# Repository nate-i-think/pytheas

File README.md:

# about pytheas
Pytheas is a custom ATSAMD21G18A-based (Cortex-M0+, arduino-compatible) flight controller which I have designed for a self-landing, thrust vectoring rocket which is being built by [Princeton Rocketry](https://www.princetonrocketry.com/) at Princeton University. Anyone is welcome to integrate it into their projects as long as they provide appropriate credit. However, no technical support is provided.

# features
 - ATSAMD21G18A microprocessor
   - Programmable via SWD (TagConnect, half-pitch DuPont) and USB
   - 10 exposed GPIO (plus 5 more extras in half-pitch)
   - Exposed I2C (recomended to connect GPS)
   - Everything else you'd expect
 - BMP390 Pressure Sensor
 - LSM6DSOXTR 6-Axis IMU
 - Power Regulation:
   - 5V @ 9A out (buck) with lots of capacitence  
   - 3v3 @ 1A out (LDO)
   - ~6–12V in

# renderings

# layers

# schematic

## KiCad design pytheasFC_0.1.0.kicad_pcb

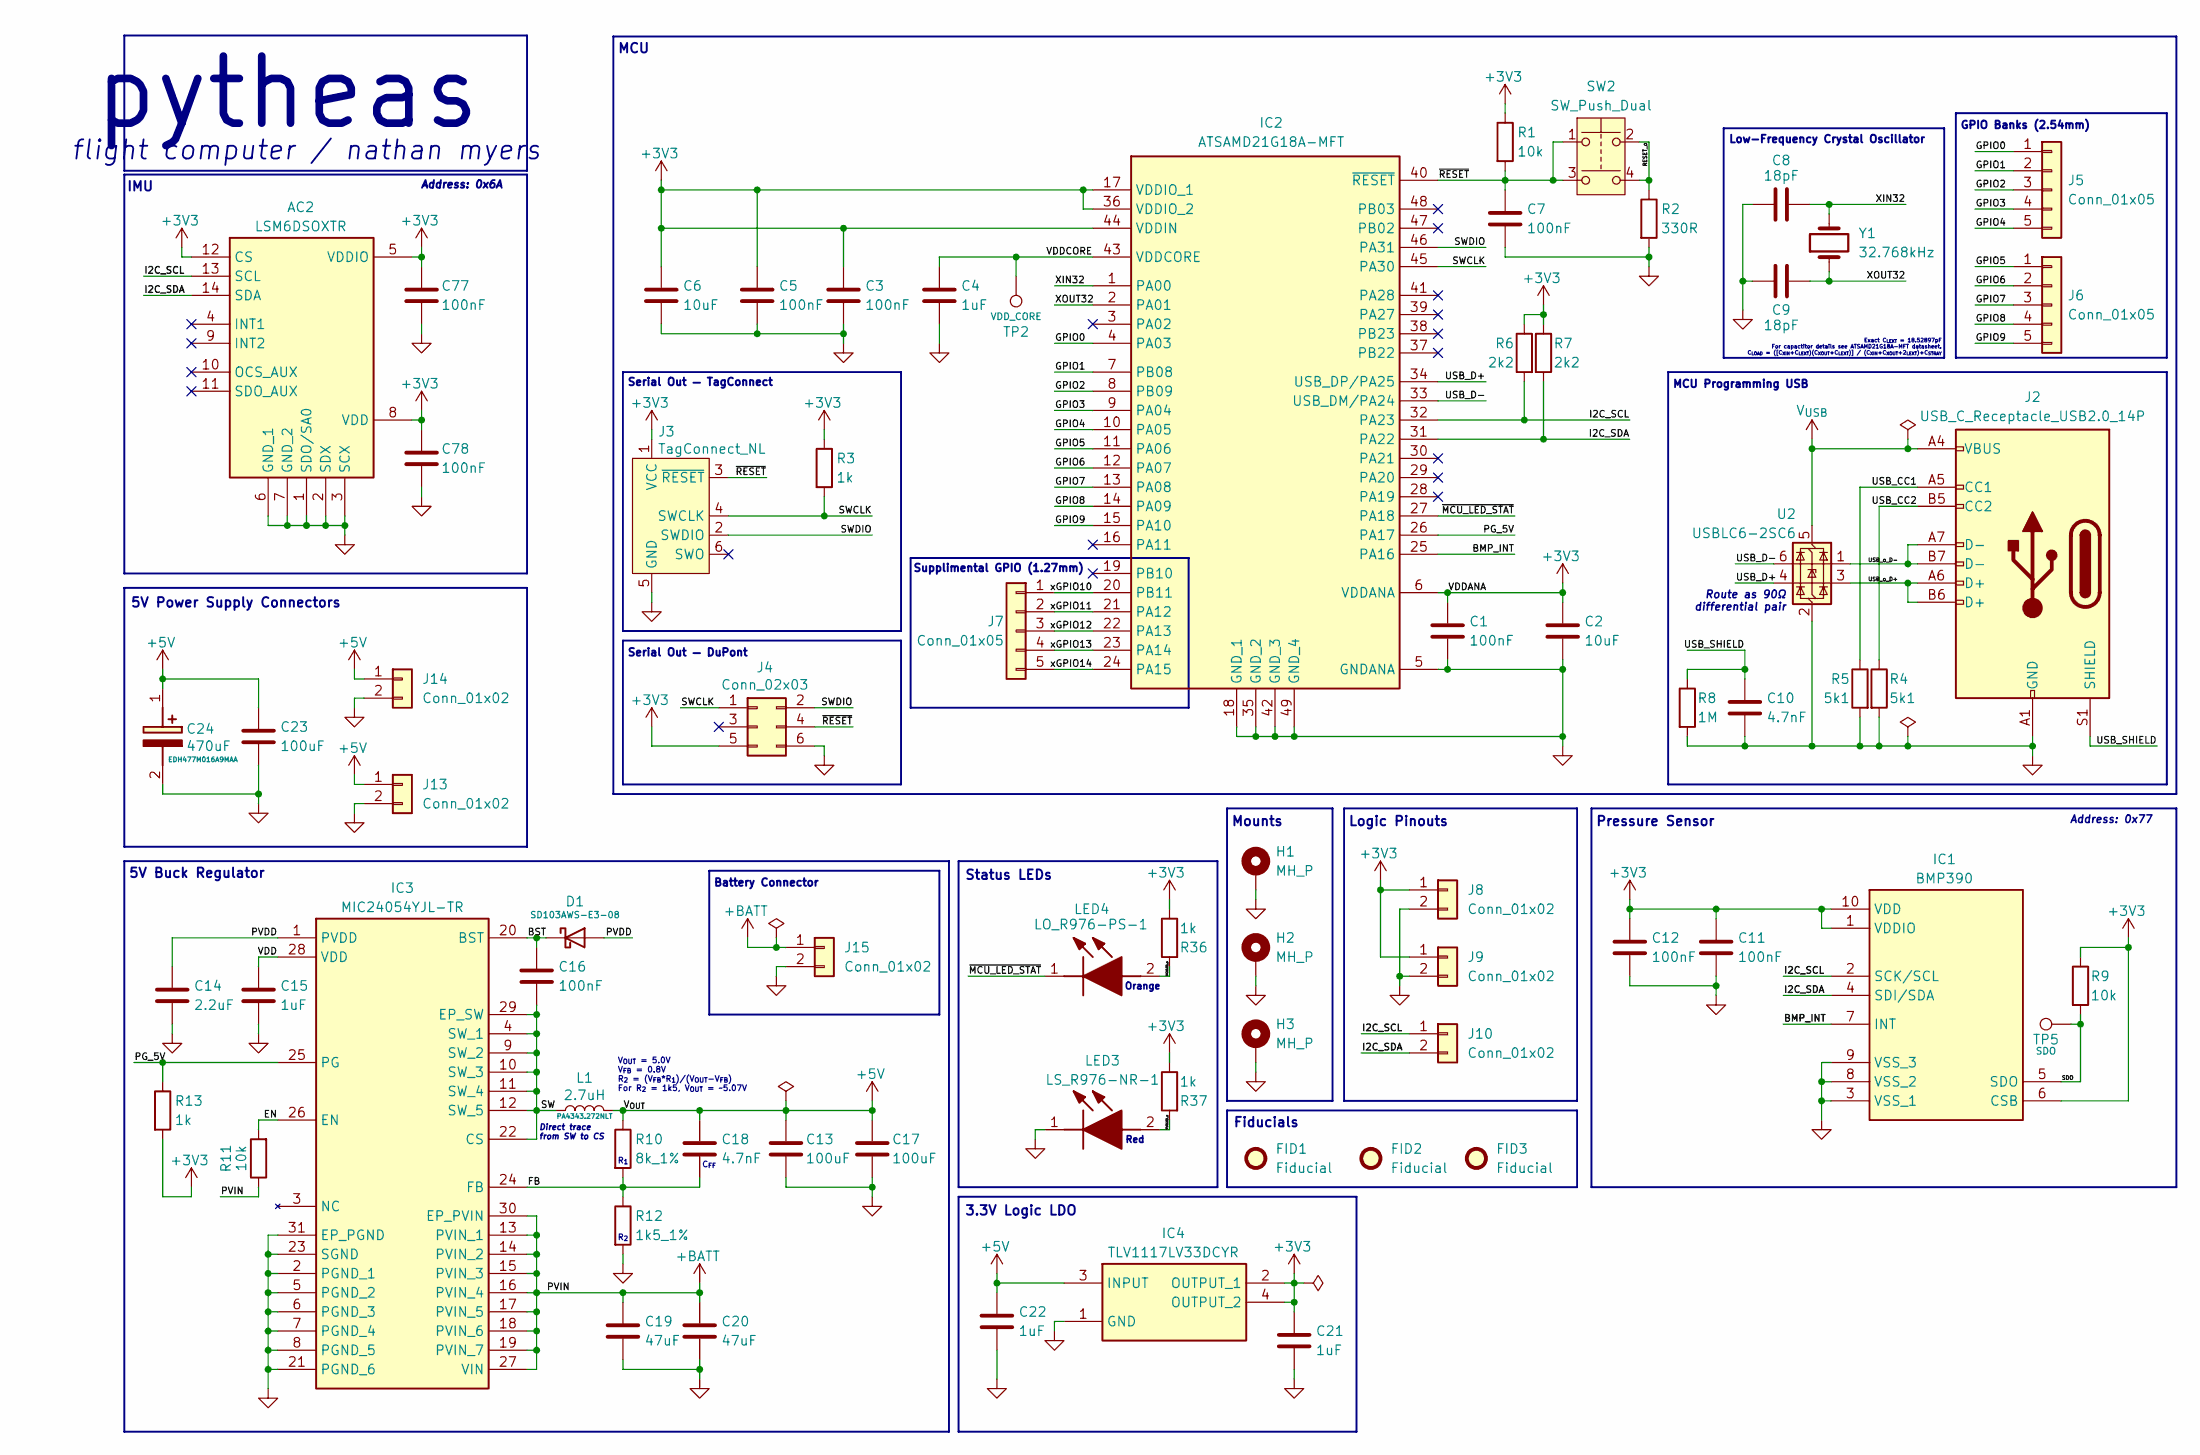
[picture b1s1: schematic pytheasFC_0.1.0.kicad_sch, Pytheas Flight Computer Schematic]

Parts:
AC2: LSM6DSOXTR; LGA-14_1; Mouser Part Number 511-LSM6DSOXTR
C1, C3, C5, C7, C11, C12, C16, C77, C78: 100nF; C_0402_1005Metric
C2, C6: 10uF; C_0805_2012Metric
C4, C15, C21, C22: 1uF; C_0805_2012Metric
C8, C9: 18pF; C_0402_1005Metric
C10, C18: 4.7nF; C_0402_1005Metric
C13, C17, C23: 100uF; C_1206_3216Metric
C14: 2.2uF; C_0805_2012Metric
C19, C20: 47uF; C_1206_3216Metric
C24: 470uF; CAPAE830X1050N; Mouser Part Number 80-EDH477M016A9MAA
D1: SD103AWS-E3-08; SOD2713X115N; Part Number SD103AWS-E3-08
FID1, FID2, FID3: Fiducial; Fiducial_1mm_Mask2mm
H1, H2, H3: MH_P; MountingHole_2.2mm_M2_Pad_Via
IC1: BMP390; Mouser Part Number 262-BMP390
IC2: ATSAMD21G18A-MFT; QFN50P700X700X90-49N-D; Mouser Part Number 556-ATSAMD21G18A-MFT
IC3: MIC24054YJL-TR; MIC24054YJLTR; Mouser Part Number 998-MIC24054YJLTR
IC4: TLV1117LV33DCYR; SOT230P700X180-4N; Mouser Part Number 595-TLV1117LV33DCYR
J2: USB_C_Receptacle_USB2.0_14P; USB_C_Receptacle_GCT_USB4105-xx-A_16P_TopMnt_Horizontal
J3: TagConnect_NL; Tag-Connect_TC2030-IDC-NL_2x03_P1.27mm_Vertical
J4: Conn_02x03; PinHeader_2x03_P1.27mm_Vertical
J5, J6: Conn_01x05; PinHeader_1x05_P2.54mm_Horizontal
J7: Conn_01x05; PinHeader_1x05_P1.27mm_Vertical
J8, J9, J10, J13, J14, J15: Conn_01x02; PinHeader_1x02_P2.54mm_Horizontal
L1: 2.7uH; INDPM140128X650N; Part Number PA4343.272NLT
LED3: LS_R976-NR-1; LEDC2012X40N; Mouser Part Number 720-LSR976-NR-1
LED4: LO_R976-PS-1; LEDC2012X90N; Mouser Part Number 720-LOR976-PS-1
R1, R9, R11: 10k; R_0402_1005Metric
R2: 330R; R_0402_1005Metric
R3, R13, R36, R37: 1k; R_0402_1005Metric
R4, R5: 5k1; R_0402_1005Metric
R6, R7: 2k2; R_0402_1005Metric
R8: 1M; R_0402_1005Metric
R10: 8k_1%; R_0402_1005Metric
R12: 1k5_1%; R_0402_1005Metric
SW2: SW_Push_Dual; FSM2J_1; Part Number 2-1437565-8
TP2: VDD_CORE; TestPoint_Pad_D2.0mm
TP5: SDO; TestPoint_Pad_D2.0mm
U2: USBLC6-2SC6; SOT-23-6
Y1: 32.768kHz; ECX-31B; Part Number ECS-.327-12.5-34B-TR

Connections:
+3V3: AC2.5 (VDDIO), AC2.8 (VDD), AC2.12 (CS), C1.1, C2.1, C3.1, C5.1, C6.1, C11.1, C12.1, C21.1, C77.1, C78.1, IC1.1 (VDDIO), IC1.6 (CSB), IC1.10 (VDD), IC2.6 (VDDANA), IC2.17 (VDDIO_1), IC2.36 (VDDIO_2), IC2.44 (VDDIN), IC4.2 (OUTPUT_1), IC4.4 (OUTPUT_2), J3.1 (VCC), J4.5, J8.1, J9.1, R1.1, R3.1, R6.1, R7.1, R9.1, R13.2, R36.1, R37.1
+5V: C13.1, C17.1, C18.1, C22.1, C23.1, C24.1 (+), IC4.3 (INPUT), J13.1, J14.1, L1.2, R10.1
+BATT: C19.1, C20.1, IC3.13 (PVIN_1), IC3.14 (PVIN_2), IC3.15 (PVIN_3), IC3.16 (PVIN_4), IC3.17 (PVIN_5), IC3.18 (PVIN_6), IC3.19 (PVIN_7), IC3.27 (VIN), IC3.30 (EP_PVIN), J15.1, R11.1
/BMP_INT: IC1.7 (INT), IC2.25 (PA16)
/BST: C16.1, D1.1 (K), IC3.20 (BST)
/EN: IC3.26 (EN), R11.2
/FB: C18.2, IC3.24 (FB), R10.2, R12.1
/GPIO0: IC2.4 (PA03), J5.1
/GPIO1: IC2.7 (PB08), J5.2
/GPIO2: IC2.8 (PB09), J5.3
/GPIO3: IC2.9 (PA04), J5.4
/GPIO4: IC2.10 (PA05), J5.5
/GPIO5: IC2.11 (PA06), J6.1
/GPIO6: IC2.12 (PA07), J6.2
/GPIO7: IC2.13 (PA08), J6.3
/GPIO8: IC2.14 (PA09), J6.4
/GPIO9: IC2.15 (PA10), J6.5
/I2C_SCL: AC2.13 (SCL), IC1.2 (SCK/SCL), IC2.32 (PA23), J10.1, R6.2
/I2C_SDA: AC2.14 (SDA), IC1.4 (SDI/SDA), IC2.31 (PA22), J10.2, R7.2
/MCULED_o: LED4.2 (A), R36.2
/PG_5V: IC2.26 (PA17), IC3.25 (PG), R13.1
/PVDD: C14.1, D1.2 (A), IC3.1 (PVDD)
/PWRLED_o: LED3.2 (A), R37.2
/RESET_o: R2.1, SW2.2, SW2.4
/SDO: IC1.5 (SDO), R9.2, TP5.1
/SW: C16.2, IC3.4 (SW_1), IC3.9 (SW_2), IC3.10 (SW_3), IC3.11 (SW_4), IC3.12 (SW_5), IC3.22 (CS), IC3.29 (EP_SW), L1.1
/SWCLK: IC2.45 (PA30), J3.4 (SWCLK), J4.1, R3.2
/SWDIO: IC2.46 (PA31), J3.2 (SWDIO), J4.2
/USB_CC1: J2.A5 (CC1), R5.1
/USB_CC2: J2.B5 (CC2), R4.1
/USB_D+: IC2.34 (USB_DP/PA25), U2.4 (I/O2)
/USB_D-: IC2.33 (USB_DM/PA24), U2.6 (I/O1)
/USB_SHIELD: C10.1, J2.S1 (SHIELD), R8.1
/USB_o_D+: J2.A6 (D+), J2.B6 (D+), U2.3 (I/O2)
/USB_o_D-: J2.A7 (D-), J2.B7 (D-), U2.1 (I/O1)
/VDD: C15.1, IC3.28 (VDD)
/VDDCORE: C4.1, IC2.43 (VDDCORE), TP2.1
/XIN32: C8.2, IC2.1 (PA00), Y1.2
/XOUT32: C9.1, IC2.2 (PA01), Y1.1
/xGPIO10: IC2.20 (PB11), J7.1
/xGPIO11: IC2.21 (PA12), J7.2
/xGPIO12: IC2.22 (PA13), J7.3
/xGPIO13: IC2.23 (PA14), J7.4
/xGPIO14: IC2.24 (PA15), J7.5
/~MCU_LED_STAT: IC2.27 (PA18), LED4.1 (K)
/~RESET: C7.1, IC2.40 (~RESET), J3.3 (~RESET), J4.4, R1.2, SW2.1, SW2.3
GND: AC2.1 (SDO/SA0), AC2.2 (SDX), AC2.3 (SCX), AC2.6 (GND_1), AC2.7 (GND_2), C1.2, C2.2, C3.2, C4.2, C5.2, C6.2, C7.2, C8.1, C9.2, C10.2, C11.2, C12.2, C13.2, C14.2, C15.2, C17.2, C19.2, C20.2, C21.2, C22.2, C23.2, C24.2 (-), C77.2, C78.2, H1.1, H2.1, H3.1, IC1.3 (VSS_1), IC1.8 (VSS_2), IC1.9 (VSS_3), IC2.5 (GNDANA), IC2.18 (GND_1), IC2.35 (GND_2), IC2.42 (GND_3), IC2.49 (GND_4), IC3.2 (PGND_1), IC3.5 (PGND_2), IC3.6 (PGND_3), IC3.7 (PGND_4), IC3.8 (PGND_5), IC3.21 (PGND_6), IC3.23 (SGND), IC3.31 (EP_PGND), IC4.1 (GND), J2.A1 (GND), J2.A12 (GND), J2.B1 (GND), J2.B12 (GND), J3.5 (GND), J4.6, J8.2, J9.2, J13.2, J14.2, J15.2, LED3.1 (K), R2.2, R4.2, R5.2, R8.2, R12.2, U2.2 (GND)
V_{USB}: J2.A4 (VBUS), J2.A9 (VBUS), J2.B4 (VBUS), J2.B9 (VBUS), U2.5 (VBUS)

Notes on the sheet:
Address: 0x6A
Pressure Sensor
Low-Frequency Crystal Oscillator
5V Buck Regulator
5V Power Supply Connectors
Serial Out — TagConnect
Logic Pinouts
Route as 90Ω differential pair
Fiducials
Address: 0x77
R_{1}
IMU
MCU
Orange
Direct trace from SW to CS
Mounts
Serial Out — DuPont
R_{2}
Battery Connector
C_{FF}
V_{OUT} = 5.0V V_{FB} = 0.8V R_{2} = (V_{FB}*R_{1})/(V_{OUT}-V_{FB}) For R_{2} = 1k5, V_{OUT} = ~5.07V
flight computer / nathan myers
GPIO Banks (2.54mm)
Exact C_{LEXT} = 18.52897pF For capactitor details see ATSAMD21G18A-MFT datasheet. C_{LOAD} = ([C_{XIN}+C_{LEXT})(C_{XOUT}+C_{LEXT})] / (C_{XIN}+C_{XOUT}+2_{LEXT})+C_{STRAY}
Status LEDs
Supplimental GPIO (1.27mm)
MCU Programming USB
3.3V Logic LDO
Red
pytheas

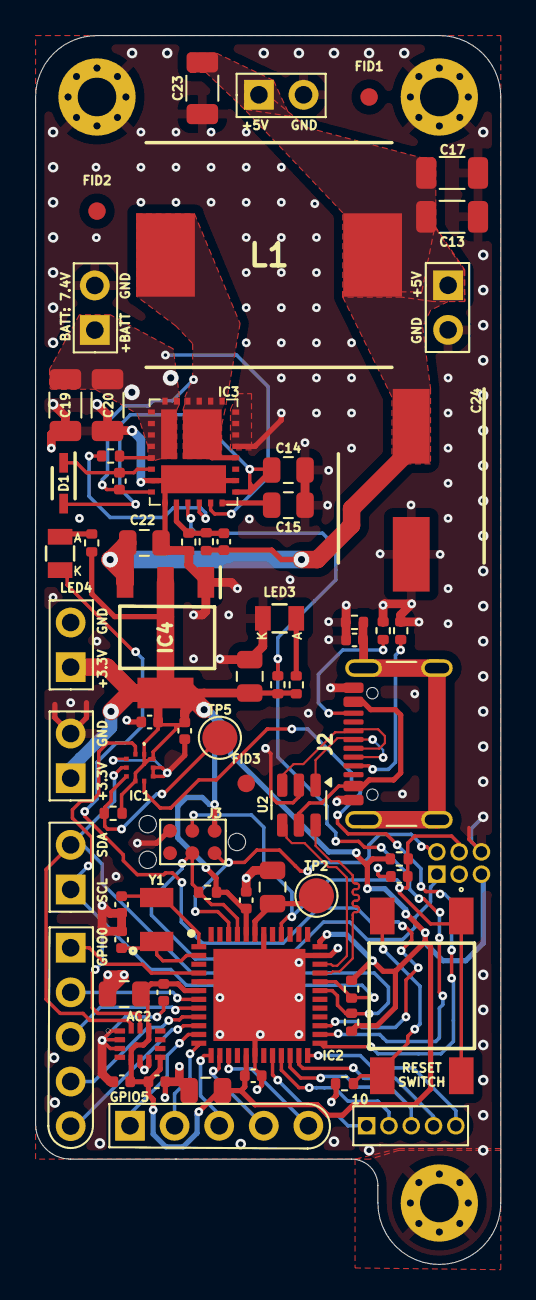
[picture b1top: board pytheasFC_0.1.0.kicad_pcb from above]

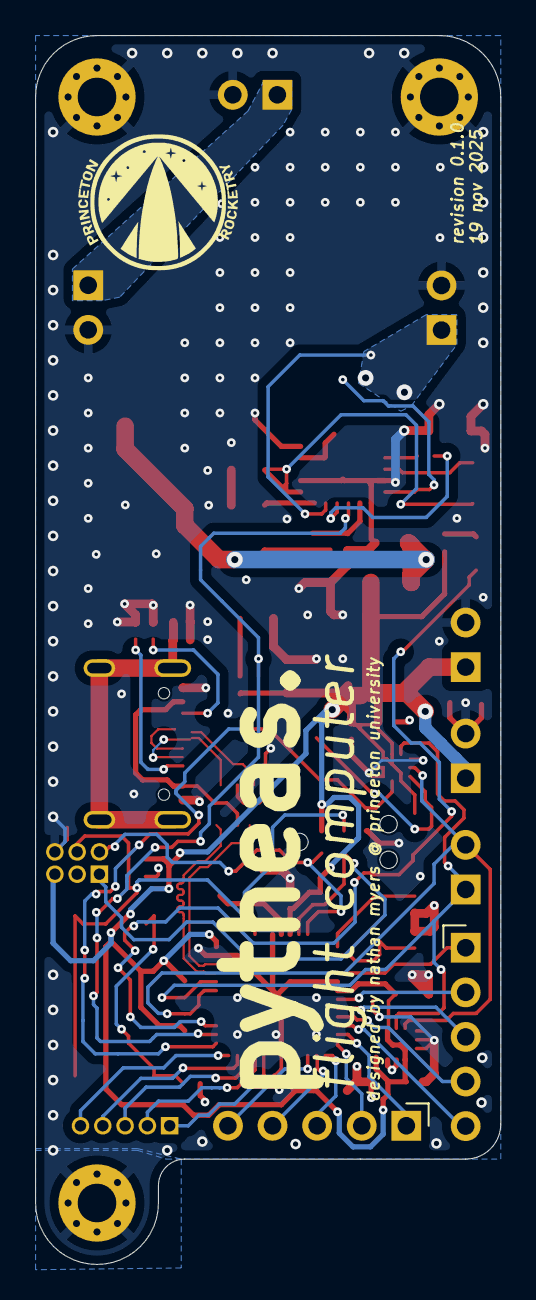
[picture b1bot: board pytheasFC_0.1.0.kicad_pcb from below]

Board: 4 copper layers, 26.5 x 70.0 mm, 73 parts (2 on the bottom side), 48 nets.

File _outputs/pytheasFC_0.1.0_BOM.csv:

Qty,Designator,Value,Footprint,Manufacturer,Manufacturer Part Number
1,AC2,LSM6DSOXTR,SamacSys_Parts:LGA-14_1,STMicroelectronics,LSM6DSOXTR
9,"C1, C3, C5, C7, C11, C12, C16, C77, C78",100nF,Capacitor_SMD:C_0402_1005Metric,,
2,"C2, C6",10uF,Capacitor_SMD:C_0805_2012Metric,,
4,"C4, C15, C21, C22",1uF,Capacitor_SMD:C_0805_2012Metric,,
2,"C8, C9",18pF,Capacitor_SMD:C_0402_1005Metric,,
2,"C10, C18",4.7nF,Capacitor_SMD:C_0402_1005Metric,,
3,"C13, C17, C23",100uF,Capacitor_SMD:C_1206_3216Metric,,
1,C14,2.2uF,Capacitor_SMD:C_0805_2012Metric,,
2,"C19, C20",47uF,Capacitor_SMD:C_1206_3216Metric,,
1,C24,470uF,SamacSys_Parts:CAPAE830X1050N,KEMET,EDH477M016A9MAA
1,D1,SD103AWS-E3-08,SamacSys_Parts:SOD2713X115N,Vishay Semiconductors, SD103AWS-E3-08 
1,IC1,BMP390,SamacSys_Parts:BMP390,BOSCH,BMP390
1,IC2,ATSAMD21G18A-MFT,SamacSys_Parts:QFN50P700X700X90-49N-D,Microchip,ATSAMD21G18A-MFT
1,IC3,MIC24054YJL-TR,SamacSys_Parts:MIC24054YJLTR,Microchip,MIC24054YJL-TR
1,IC4,TLV1117LV33DCYR,SamacSys_Parts:SOT230P700X180-4N,Texas Instruments,TLV1117LV33DCYR
1,J2,USB_C_Receptacle_USB2.0_14P,Connector_USB:USB_C_Receptacle_GCT_USB4105-xx-A_16P_TopMnt_Horizontal,GCT ,USB4105-GF-A 
1,L1,2.7uH,SamacSys_Parts:INDPM140128X650N,PULSE,PA4343.272NLT
1,LED3,LS_R976-NR-1,SamacSys_Parts:LEDC2012X40N,ams OSRAM,LS R976-NR-1
1,LED4,LO_R976-PS-1,SamacSys_Parts:LEDC2012X90N,ams OSRAM,LO R976-PS-1
3,"R1, R9, R11",10k,Capacitor_SMD:C_0402_1005Metric,,
1,R2,330R,Capacitor_SMD:C_0402_1005Metric,,
2,"R3, R13",1k,Capacitor_SMD:C_0402_1005Metric,,
2,"R4, R5",5k1,Capacitor_SMD:C_0402_1005Metric,,
2,"R6, R7",2k2,Capacitor_SMD:C_0402_1005Metric,,
1,R8,1M,Capacitor_SMD:C_0402_1005Metric,,
1,R10,8k_1%,Capacitor_SMD:C_0402_1005Metric,,
1,R12,1k5_1%,Capacitor_SMD:C_0402_1005Metric,,
2,"R36, R37",1k,Resistor_SMD:R_0402_1005Metric,,
1,SW2,SW_Push_Dual,SamacSys_Parts:FSM2J_1,TE Connectivity / P&B , 2-1437565-8 
1,U2,USBLC6-2SC6,Package_TO_SOT_SMD:SOT-23-6,STMicroelectronics ,USBLC6-2SC6 
1,Y1,32.768kHz,SamacSys_Parts:ECX-31B,ECS , ECS-.327-12.5-34B-TR

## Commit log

2025-11-21 initial commit, pytheas 0.1.0
2025-11-21 Revise README
2025-11-21 add schematic
2025-11-21 Update README with images
2025-11-21 fix uh oh
2025-11-26 Update README with GPS connection recommendation
2025-11-27 Update Mounting Hole Positions
2025-12-23 update VDDANA net and connections
2025-12-27 modify CPL
2025-12-27 modify CPL againnn
